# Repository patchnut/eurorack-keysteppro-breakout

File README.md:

# eurorack-keysteppro-breakout
breakout module for the cv and gate connections of the keystep pro

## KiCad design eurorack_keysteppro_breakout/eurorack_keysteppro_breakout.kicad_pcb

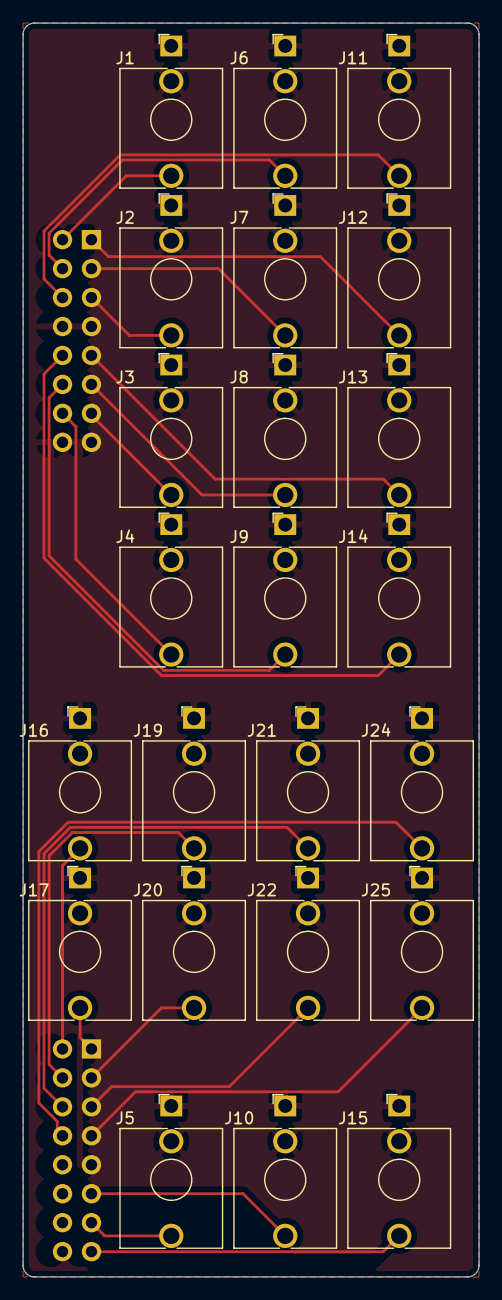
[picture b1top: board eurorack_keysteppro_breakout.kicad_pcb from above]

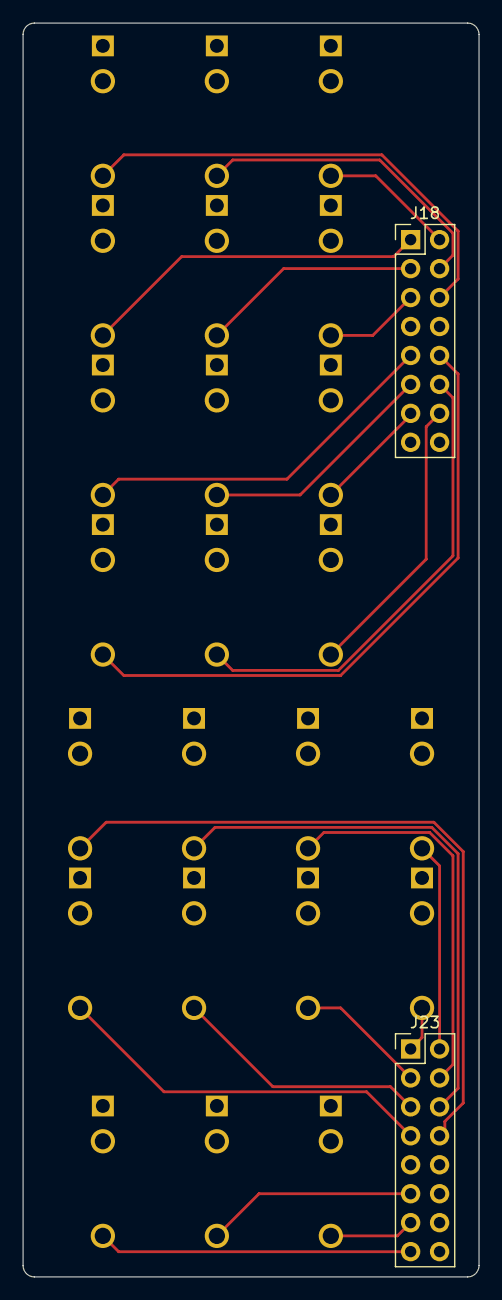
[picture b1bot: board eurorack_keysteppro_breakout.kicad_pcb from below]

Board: 2 copper layers, 40.0 x 110.0 mm, 25 parts (2 on the bottom side), 24 nets.

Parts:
J1, J2, J3, J4, J5, J6, J7, J8, J9, J10, J11, J12, J13, J14, J15, J16, J17, J19, J20, J21, J22, J24, J25: AudioJack2_SwitchT; Jack_3.5mm_QingPu_WQP-PJ398SM_Vertical_CircularHoles
J18, J23: Conn_02x08_Odd_Even; PinHeader_2x08_P2.54mm_Vertical

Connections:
GND: J1.S, J1.TN, J2.S, J2.TN, J3.S, J3.TN, J4.S, J4.TN, J5.S, J5.TN, J6.S, J6.TN, J7.S, J7.TN, J8.S, J8.TN, J9.S, J9.TN, J10.S, J10.TN, J11.S, J11.TN, J12.S, J12.TN, J13.S, J13.TN, J14.S, J14.TN, J15.S, J15.TN, J16.S, J16.TN, J17.S, J17.TN, J18.7, J18.8, J18.15, J18.16, J19.S, J19.TN, J20.S, J20.TN, J21.S, J21.TN, J22.S, J22.TN, J23.9, J24.S, J24.TN, J25.S, J25.TN
ck_in: J5.T, J23.13
ck_out: J10.T, J23.11
ck_rst: J15.T, J23.15
cv1: J1.T, J18.2
cv2: J2.T, J18.5
cv3: J3.T, J18.13
cv4: J4.T, J18.14
dr1: J16.T, J23.2
dr2: J19.T, J23.4
dr3: J21.T, J23.6
dr4: J23.8, J24.T
dr5: J17.T, J23.1
dr6: J20.T, J23.3
dr7: J22.T, J23.5
dr8: J23.7, J25.T
gt1: J6.T, J18.4
gt2: J7.T, J18.3
gt3: J8.T, J18.11
gt4: J9.T, J18.12
md1: J11.T, J18.6
md2: J12.T, J18.1
md3: J13.T, J18.9
md4: J14.T, J18.10

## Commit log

2021-11-20 init project, add first connector
2021-11-20 add all connectors to schema and wire stuff up
2021-11-20 annotate and fix some rules checker issues
2021-11-20 fix audio jack footprints
2021-11-20 roughly layout connectors
2021-11-20 fix pinheaders, flip to backside board
2021-11-20 some layout
2021-12-11 route traces for gate/trigger/mod and clock signals
2021-12-11 reorder pins on clock and trigger header, route the rest of the tracks
